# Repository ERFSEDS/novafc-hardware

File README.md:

# Nova Flight Computer

Rev 1.0 hardware:
STM32F401RBTx
USBC - FTDI chip connecting usb to UART2
3 pYRO Channels
SD Card
Flash Chip
High-g Accel: H3LIS331DL
Barometer: MS560702BA03-50
IMU: BMI088
SWDIO

Rev 2.5 hardware:
STM32F411CEUx
USBC
4 Pyro Channels
SD Card
Flash Chip
High-g Accel: H3LIS331DL
Barometer: MS560702BA03-50
IMU: MPU-9250
SWDIO + SWO

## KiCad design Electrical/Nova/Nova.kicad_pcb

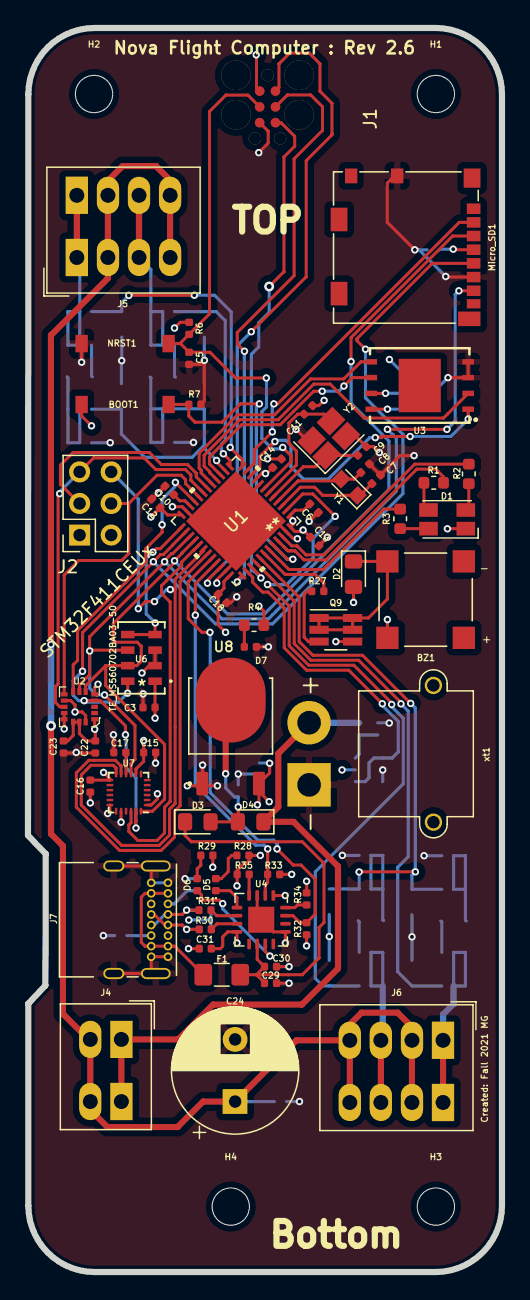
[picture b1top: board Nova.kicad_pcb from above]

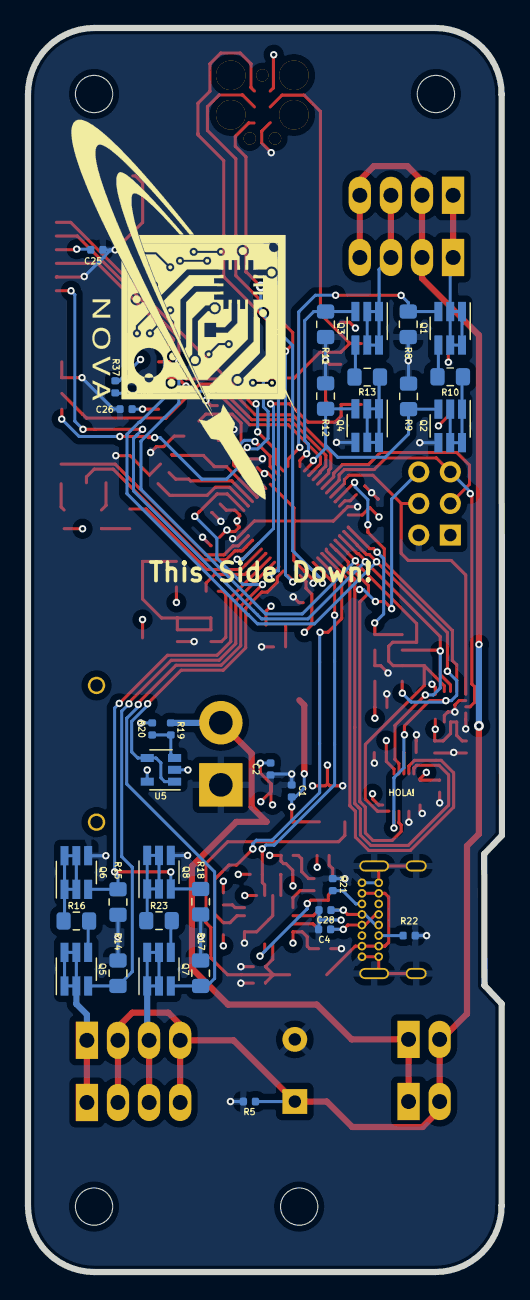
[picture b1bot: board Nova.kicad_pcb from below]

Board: 4 copper layers, 38.1 x 100.1 mm, 102 parts (33 on the bottom side), 79 nets.

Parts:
BOOT1: SW_Push; KSR223GLFG
BZ1: Buzzer; XDCR_CMT-7525-80-SMT-TR
C1, C2, C22: 10uF; C_0402_1005Metric
C3, C5, C6, C12, C13, C14, C16, C17, C18, C23, C25, C29: 100nF; C_0402_1005Metric
C4, C28: 27pF; C_0402_1005Metric
C7, C8, C9, C11: 8pF; C_0402_1005Metric
C10, C30: 4.7uF; C_0402_1005Metric
C15, C31: 10nF; C_0402_1005Metric
C24: 1mF; CP_Radial_D10.0mm_P5.00mm
C26: 0.1uF; C_0402_1005Metric
D1: ASMB-MTB0-0A3A2; LED_Avago_PLCC4_3.2x2.8mm_CW
D2, D3, D4: DIODE; D_0805_2012Metric_Pad1.15x1.40mm_HandSolder
D5, D6, D7: LED; LED_0402_1005Metric
F1: 500mA; Fuse_1206_3216Metric_Pad1.42x1.75mm_HandSolder
H1, H2, H3, H4: MountingHole; MountingHole_3mm
J1: Conn_01x06_Male; j-link_6_pin_needle
J2: Conn_02x04_Counter_Clockwise; PinSocket_2x03_P2.54mm_Vertical
J4: Conn_01x02_Female; TerminalBlock_Phoenix_PTSM-0,5-2-2.5-H-THR_1x02_P2.50mm_Hor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
J5, J6: Conn_01x04_Female; TerminalBlock_Phoenix_PTSM-0,5-4-2.5-H-THR_1x04_P2.50mm_Hor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
J7: USB_C_Receptacle_USB2.0; USB_C_Receptacle_GCT_USB4085
Micro_SD1: WE_693072010801; microSD_HC_Molex_104031-0811
NRST1: SW_Push; KSR223GLFG
Q1, Q2, Q3, Q4, Q5, Q6, Q7, Q8, Q9: Q_NMOS_DGS; SOT-23-6_Handsoldering
R1, R2, R3: 330; R_0603_1608Metric
R4: 5.1k; R_0603_1608Metric
R5, R6, R7, R37: 10k; R_0402_1005Metric
R8, R9, R11, R12, R14, R15, R17, R18: 10k; R_0805_2012Metric_Pad1.15x1.40mm_HandSolder
R10, R13, R16, R23: 3.3; R_0805_2012Metric_Pad1.15x1.40mm_HandSolder
R19: 95.5k; R_0402_1005Metric
R20: 47k; R_0402_1005Metric
R21, R22: 5k; R_0402_1005Metric
R27: 180; R_0402_1005Metric
R28, R29: 270; R_0402_1005Metric
R30, R31, R32, R33, R34, R35: 27; R_0402_1005Metric
U1: STM32F411CEUx; STM32F411CEU6
U2: ST_H3LIS331DL; TFLGA-16_3x3mm
U3: WB_W25N512GVPIT; SON127P800X600X80-9N
U4: FT230XQ; QFN-16-1EP_4x4mm_P0.65mm_EP2.1x2.1mm
U5: OP179GRT; SOT-23-5
U6: TE_MS560702BA03-50; MS560702BA03-50
U7: MPU-9250; InvenSense_QFN-24_3x3mm_P0.4mm
U8: NCP1117-3.3_TO252; DPAK228P968X238-4N
Y1: 32.768kHz; Crystal_SMD_2012-2Pin_2.0x1.2mm_HandSoldering
Y2: 25MHz; Crystal_SMD_EuroQuartz_X22-4Pin_2.5x2.0mm_HandSoldering
xt1: Conn_01x02; AMASS_XT30PW-M_1x02_P2.50mm_Horizontal

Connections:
+3V3: BOOT1.2, BZ1.1 (-), C2.2, C3.1, C6.1, C12.1, C13.1, C14.1, C15.1, C16.1, C18.1, C22.1, C23.2, C25.2, C26.2, C31.2, D1.1 (A), D2.2 (A), J1.1, J2.1, Micro_SD1.4 (VDD), R4.2, R6.1, R28.2, R29.1, R32.1, R33.1, R34.1, R35.1, R37.1, U1.1 (VBAT), U1.9 (VDDA), U1.24 (VDD), U1.36 (VDD), U1.48 (VDD), U2.1 (Vdd_IO), U2.14 (Vdd), U2.15 (Reserved), U3.8 (VCC), U4.1 (VCCIO), U4.8 (3V3OUT), U5.2 (V+), U6.1 (VDD), U7.1 (RESV_VDDIO), U7.8 (VDDIO), U7.13 (VDD), U8.2 (VO)
+BATT: D4.1 (K), J4.1, R19.1, xt1.2
/32CLOCKIN: C7.1, U1.3 (PC14), Y1.1
/32CLOCKOUT: C8.1, U1.4 (PC15), Y1.2
/ACCELEROMETER_CS: U1.21 (PB10), U2.8 (CS)
/ACCEL_INT1: J2.5, U1.19 (PB1), U2.11 (INT_1)
/ACCEL_INT2: J2.4, U1.20 (PB2), U2.9 (INT_2)
/ARM1: Q2.3 (S), Q4.3 (S), R9.1, R12.1, U1.14 (PA4)
/ARM2: Q6.3 (S), Q8.3 (S), R15.1, R18.1, U1.41 (PB5)
/BAROMETER_CS: U1.25 (PB12), U6.4 (SCB), U6.5 (SCB)
/BOOT0: BOOT1.1, R7.1, U1.44 (BOOT0)
/BUZZER: R27.2, U1.42 (PB6)
/CLOCKIN: C9.1, U1.5 (PH0), Y2.1
/CLOCKOUT: C11.1, U1.6 (PH1), Y2.3
/FIRE1: Q1.3 (S), R8.1, U1.12 (PA2)
/FIRE2: Q3.3 (S), R11.1, U1.13 (PA3)
/FIRE3: Q5.3 (S), R14.1, U1.40 (PB4)
/FIRE4: Q7.3 (S), R17.1, U1.2 (PC13)
/FL_CS: U1.10 (PA0), U3.1 (/CS)
/FSYNC: U1.31 (PA10), U7.11 (FSYNC)
/GPIO1: J2.3, U1.18 (PB0)
/IMU_CS: U1.29 (PA8), U7.22 (~CS)
/IMU_INT: J2.6, U1.30 (PA9), U7.12 (INT)
/LED_BLUE: R3.2, U1.43 (PB7)
/LED_GREEN: R1.2, U1.45 (PB8)
/LED_RED: R2.2, U1.46 (PB9)
/NRST: C5.2, J1.3, NRST1.2, R6.2, U1.7 (NRST)
/Pyro Channels/PYRO1: J5.1, Q1.1 (D), Q1.2, Q1.5, Q1.6
/Pyro Channels/PYRO2: J5.3, Q3.1 (D), Q3.2, Q3.5, Q3.6
/Pyro Channels/PYRO3: J6.1, Q5.1 (D), Q5.2, Q5.5, Q5.6
/Pyro Channels/PYRO4: J6.3, Q7.1 (D), Q7.2, Q7.5, Q7.6
/RXD: R33.2, U1.33 (PA12), U4.2 (RXD)
/SD_CS: Micro_SD1.2 (DAT3/CD), U1.11 (PA1)
/SPI1_MISO: U1.16 (PA6), U3.2 (DO(IO1))
/SPI1_MOSI: U1.17 (PA7), U3.5 (DI(IO0))
/SPI1_SCLK: U1.15 (PA5), U3.6 (CLK)
/SPI2_MISO: Micro_SD1.7 (DAT0), U1.27 (PB14), U2.7 (SDO/SA0), U6.6 (SDO), U7.9 (AD0/MISO)
/SPI2_MOSI: Micro_SD1.3 (CMD), U1.28 (PB15), U2.6 (SDA/SDI/SDO), U6.7 (SDI/SDA), U7.24 (SDA/MOSI)
/SPI2_SCLK: Micro_SD1.5 (CLK), U1.26 (PB13), U2.4 (SCL/SPC), U6.8 (SCLK), U7.23 (SCL/SCLK)
/SWCLK: J1.4, U1.37 (PA14)
/SWDIO: J1.2, U1.34 (PA13)
/SWO: J1.6, U1.39 (PB3)
/TXD: R32.2, U1.32 (PA11), U4.15 (TXD)
/USB-C/D+: R31.2, U4.6 (USBDP)
/USB-C/D-: R30.1, U4.7 (USBDM)
/USB-C/_N: C4.1, J7.A7 (D-), J7.B7 (D-), R30.2
/USB-C/_P: C28.1, J7.A6 (D+), J7.B6 (D+), R31.1
/VCAP: C10.1, U1.22 (VCAP1)
/VMonitor: U1.38 (PA15), U5.1, U5.4 (-)
GND: C1.1, C2.1, C3.2, C4.2, C5.1, C6.2, C7.2, C8.2, C9.2, C10.2, C11.2, C12.2, C13.2, C14.2, C15.2, C16.2, C17.2, C18.2, C22.2, C23.1, C24.2, C25.1, C26.1, C28.2, C29.1, C30.1, C31.1, D7.1 (K), J1.5, J2.2, J7.A1 (GND), J7.A12 (GND), J7.B1 (GND), J7.B12 (GND), J7.S1 (SHIELD), Micro_SD1.6 (VSS), Micro_SD1.9 (SHIELD), NRST1.1, Q2.4, Q4.4, Q6.4, Q8.4, Q9.4, R5.2, R7.2, R8.2, R9.2, R11.2, R12.2, R14.2, R15.2, R17.2, R18.2, R20.2, R21.1, R22.2, U1.8 (VSSA), U1.23 (VSS), U1.35 (VSS), U1.47 (VSS), U1.49 (VSS), U2.5 (GND), U2.10 (Reserved), U2.12 (GND), U2.13 (GND), U2.16 (GND), U3.3 (/WP(IO2)), U3.4 (GND), U4.3 (GND), U4.13 (GND), U4.17 (GND), U5.5 (V-), U6.2 (PS), U6.3 (GND), U7.18 (GND), U7.20 (RESV_GND), U8.1 (GND), Y2.2, Y2.4, xt1.1
unnamed: BZ1.2 (+), D2.1 (K), Q9.1 (D), Q9.2, Q9.5, Q9.6
unnamed: C1.2, D3.2 (A), D4.2 (A), U8.3 (VI)
unnamed: C17.1, U7.10 (REGOUT)
unnamed: C24.1, J4.2, J5.2, J5.4, J6.2, J6.4, R5.1
unnamed: D1.2 (BK), R3.1
unnamed: D1.3 (GK), R1.1
unnamed: D1.4 (RK), R2.1
unnamed: D5.1 (K), U4.5 (CBUS2)
unnamed: D5.2 (A), R28.1
unnamed: D6.1 (K), U4.11 (CBUS1)
unnamed: D6.2 (A), R29.2
unnamed: D7.2 (A), R4.1
unnamed: F1.2, J7.A4 (VBUS), J7.A9 (VBUS), J7.B4 (VBUS), J7.B9 (VBUS)
unnamed: J7.A5 (CC1), R21.2
unnamed: J7.B5 (CC2), R22.1
unnamed: Q1.4, R10.1
unnamed: Q2.1 (D), Q2.2, Q2.5, Q2.6, R10.2
unnamed: Q3.4, R13.1
unnamed: Q4.1 (D), Q4.2, Q4.5, Q4.6, R13.2
unnamed: Q5.4, R16.1
unnamed: Q6.1 (D), Q6.2, Q6.5, Q6.6, R16.2
unnamed: Q7.4, R23.1
unnamed: Q8.1 (D), Q8.2, Q8.5, Q8.6, R23.2
unnamed: Q9.3 (S), R27.1
unnamed: R19.2, R20.1, U5.3 (+)
unnamed: R34.2, U4.16 (~RTS)
unnamed: R35.2, U4.4 (~CTS)
unnamed: R37.2, U3.7 (/HOLD(IO3))
VBUS: C29.2, C30.2, D3.1 (K), F1.1, U4.10 (VCC)

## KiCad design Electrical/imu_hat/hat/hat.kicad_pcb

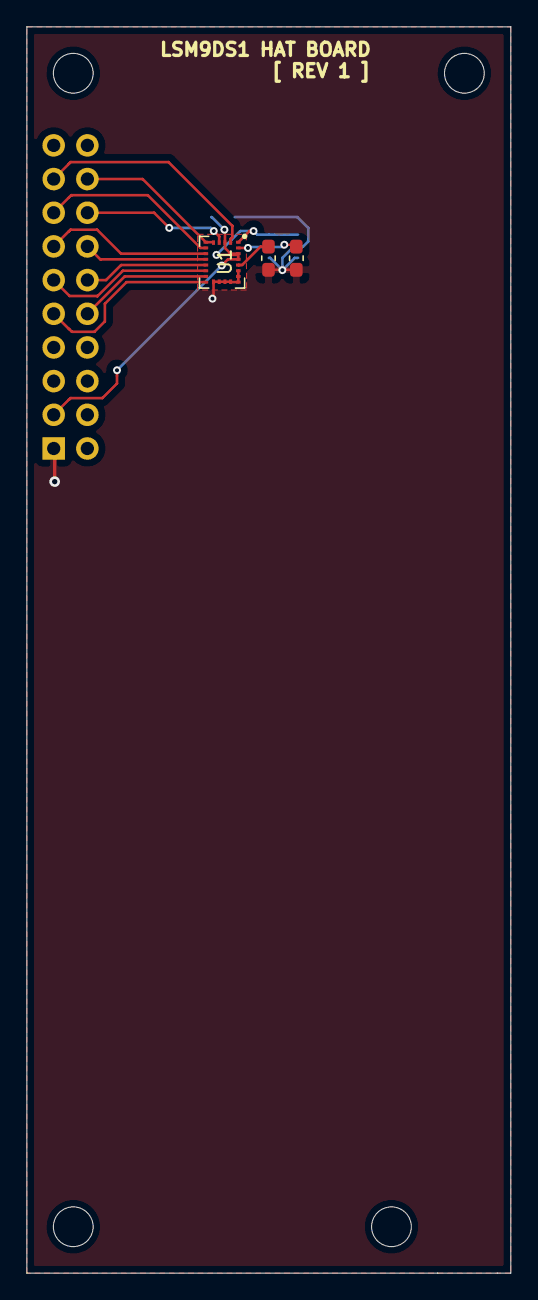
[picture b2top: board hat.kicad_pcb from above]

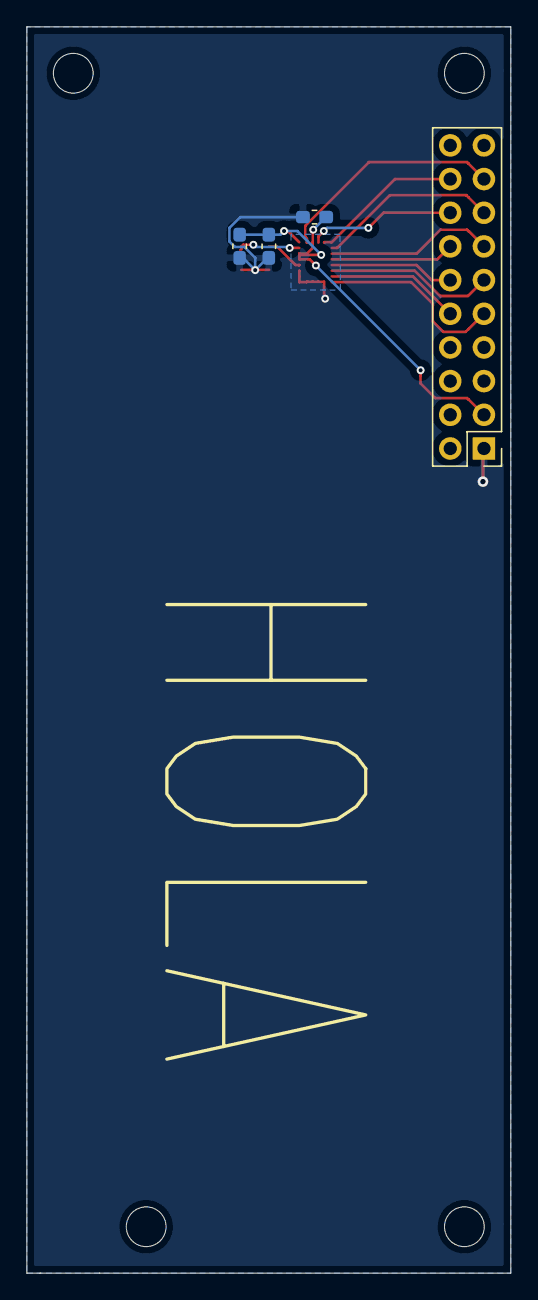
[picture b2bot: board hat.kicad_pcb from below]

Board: 2 copper layers, 36.5 x 94.0 mm, 11 parts (4 on the bottom side), 14 nets.

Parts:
C1: 10nF; C_0603_1608Metric_Pad1.05x0.95mm_HandSolder
C2, C3, C4: 100nF; C_0603_1608Metric_Pad1.05x0.95mm_HandSolder
C5: 10uF; C_0603_1608Metric_Pad1.05x0.95mm_HandSolder
H1, H2, H3, H4: MountingHole; MountingHole_3mm
J1: Conn_02x10_Odd_Even; PinHeader_2x10_P2.54mm_Vertical
U1: LSM9DS1; LGA-24L_3x3.5mm_P0.43mm

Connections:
+3V3: C2.1, C4.1, C5.1, J1.3, U1.1, U1.3, U1.22, U1.23
/CS: J1.15, U1.7
/CSM: J1.13, U1.8
/DEN: J1.9, U1.13
/DRDYM: J1.14, U1.9
/INT1: J1.11, U1.11
/INT2: J1.10, U1.12
/INTM: J1.12, U1.10
/MISO: J1.18, U1.5, U1.6
/MOSI: J1.16, U1.4
/SCLK: J1.17, U1.2
GND: C1.2, C2.2, C3.2, C4.2, C5.2, J1.1, U1.14, U1.15, U1.16, U1.17, U1.18, U1.19, U1.20
unnamed: C1.1, U1.21
unnamed: C3.1, U1.24

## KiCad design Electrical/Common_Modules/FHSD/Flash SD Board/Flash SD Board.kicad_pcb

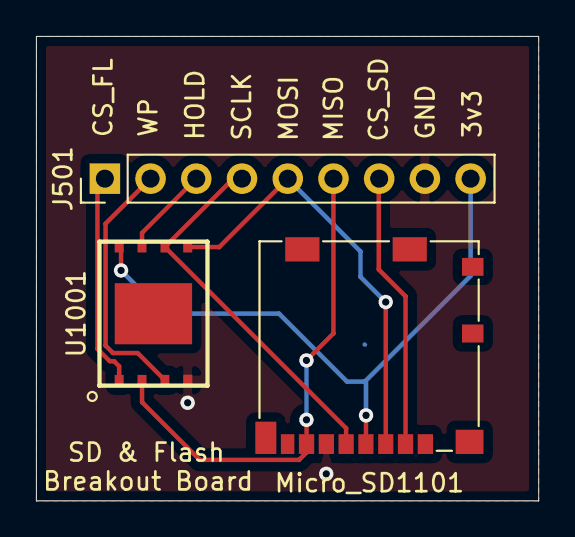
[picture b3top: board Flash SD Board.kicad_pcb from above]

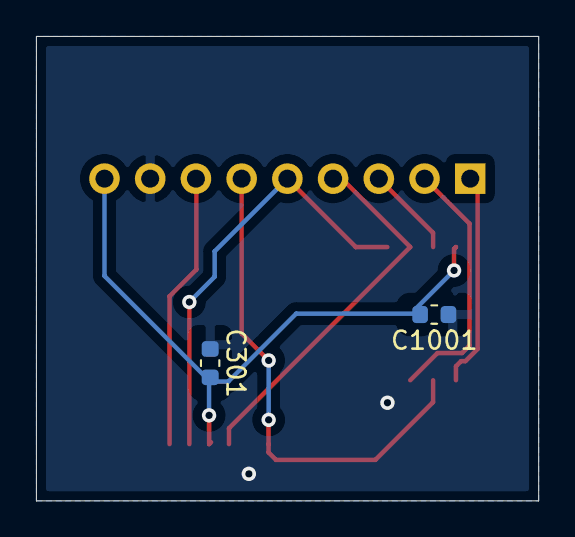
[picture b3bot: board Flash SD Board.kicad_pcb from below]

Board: 2 copper layers, 27.9 x 25.8 mm, 5 parts (2 on the bottom side), 9 nets.

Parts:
C301, C1001: 100nF; C_0603_1608Metric
J501: Conn_01x07_Male; PinHeader_1x09_P2.54mm_Vertical
Micro_SD1101: Micro_SD_Card; microSD_HC_Molex_104031-0811
U1001: W25N512GVPIT

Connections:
+3V3: C301.2, C1001.2, J501.9, Micro_SD1101.4, U1001.8
/main/Flash Chip/CS_FLASH: J501.1, U1001.1
/main/Flash Chip/HOLD: J501.3, U1001.7
/main/Flash Chip/MISO: J501.6, Micro_SD1101.7, U1001.2
/main/Flash Chip/MOSI: J501.5, Micro_SD1101.3, U1001.5
/main/Flash Chip/SCLK: J501.4, Micro_SD1101.5, U1001.6
/main/Flash Chip/WP: J501.2, U1001.3
/main/Headers/CS_SD: J501.7, Micro_SD1101.2
GND: C301.1, C1001.1, J501.8, Micro_SD1101.6, U1001.4

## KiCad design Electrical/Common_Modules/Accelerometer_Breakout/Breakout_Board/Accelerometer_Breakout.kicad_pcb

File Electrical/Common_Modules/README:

This folder is where any circuit section that may be used multiple times is put, for example firing circuit

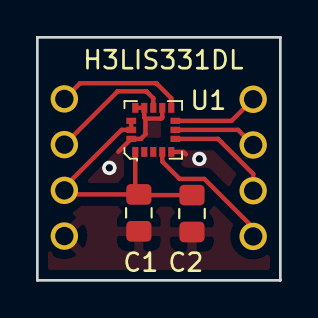
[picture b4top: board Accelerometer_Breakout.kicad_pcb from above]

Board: 2 copper layers, 13.5 x 13.5 mm, 5 parts (0 on the bottom side), 8 nets.

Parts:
C1: 10uf; C_0805_2012Metric_Pad1.15x1.40mm_HandSolder
C2: 0.1uf; C_0805_2012Metric_Pad1.15x1.40mm_HandSolder
U1: H3LIS331DL; TFLGA-16_3x3mm
U2, U3: 4_Pin_header; 4_Pin_Header

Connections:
+3V3: C1.1, C2.2, U1.1, U1.14, U1.15, U2.3
/H3LIS331DL_Accelerometer/CS_ACC: U1.8, U3.4
/H3LIS331DL_Accelerometer/INT_1_ACC: U1.11, U2.2
/H3LIS331DL_Accelerometer/INT_2_ACC: U1.9, U2.1
/H3LIS331DL_Accelerometer/SCL_ACC: U1.4, U3.1
/H3LIS331DL_Accelerometer/SDA_ACC: U1.6, U3.2
/H3LIS331DL_Accelerometer/SDO_ACC: U1.7, U3.3
GND: C1.2, C2.1, U1.5, U1.10, U1.12, U1.13, U1.16, U2.4

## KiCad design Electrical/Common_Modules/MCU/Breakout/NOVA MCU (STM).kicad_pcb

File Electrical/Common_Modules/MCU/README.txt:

This is the Nova Rev 1 Microcontroller Breakout Board. 
Because of the nature of the part, pseudo code will not be written. 
Pseudo code for this part IS the software for Nova. 

Notes: 

Programmable through SWD
debug from USB-C 

3V3 Level logic and voltage levels. 

Fuse and Tantalum capacitor has similar, but different footprints to other parts on the board

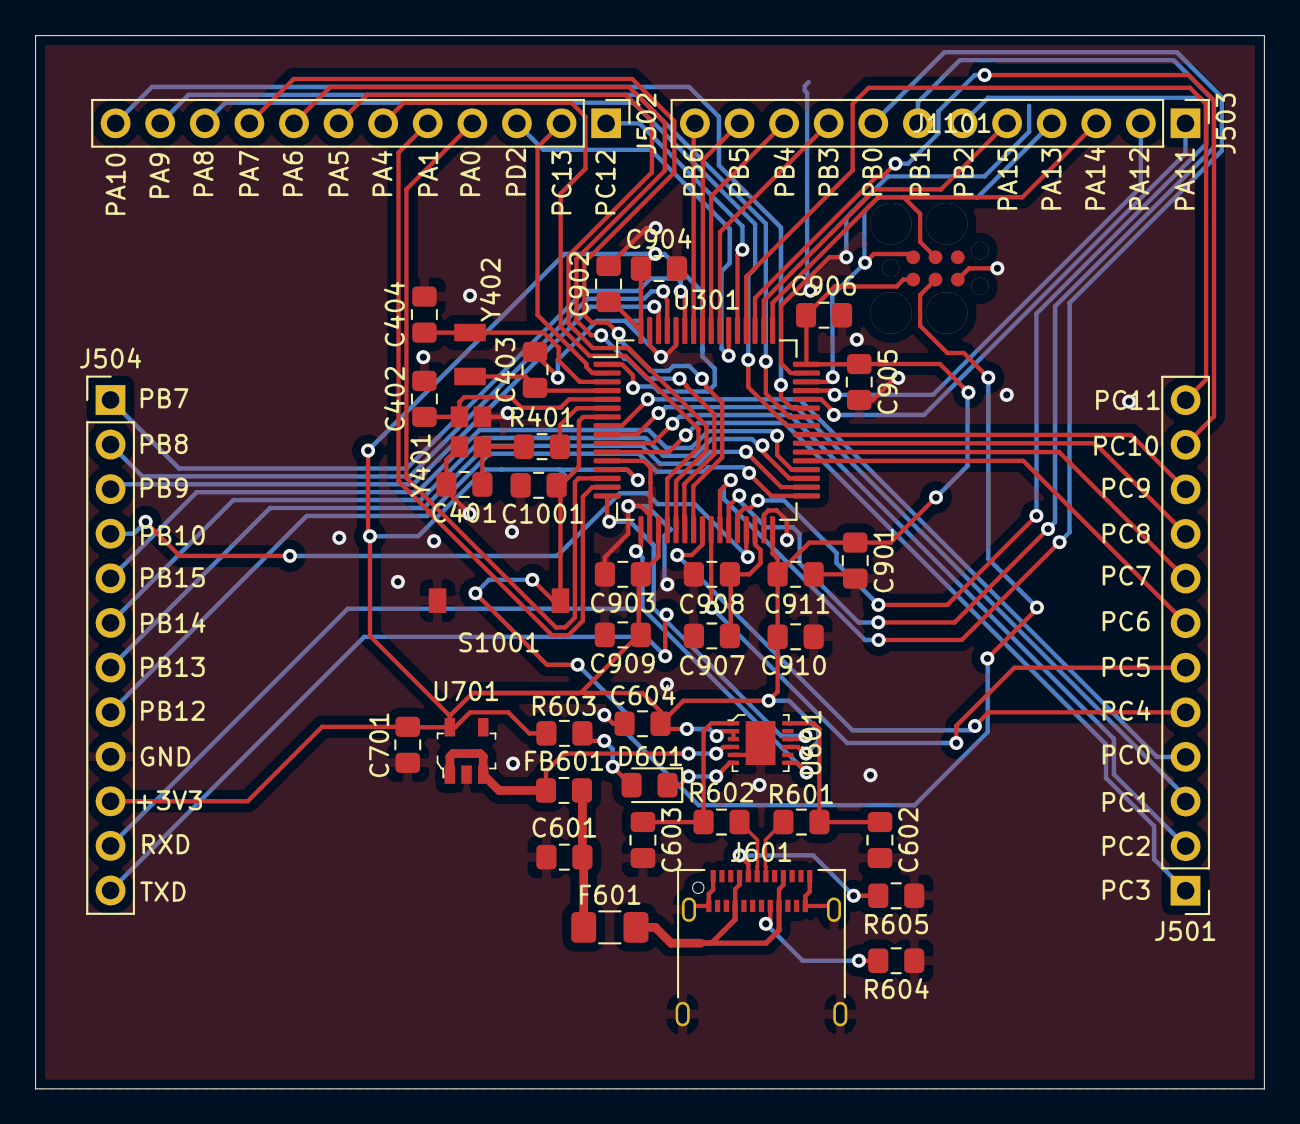
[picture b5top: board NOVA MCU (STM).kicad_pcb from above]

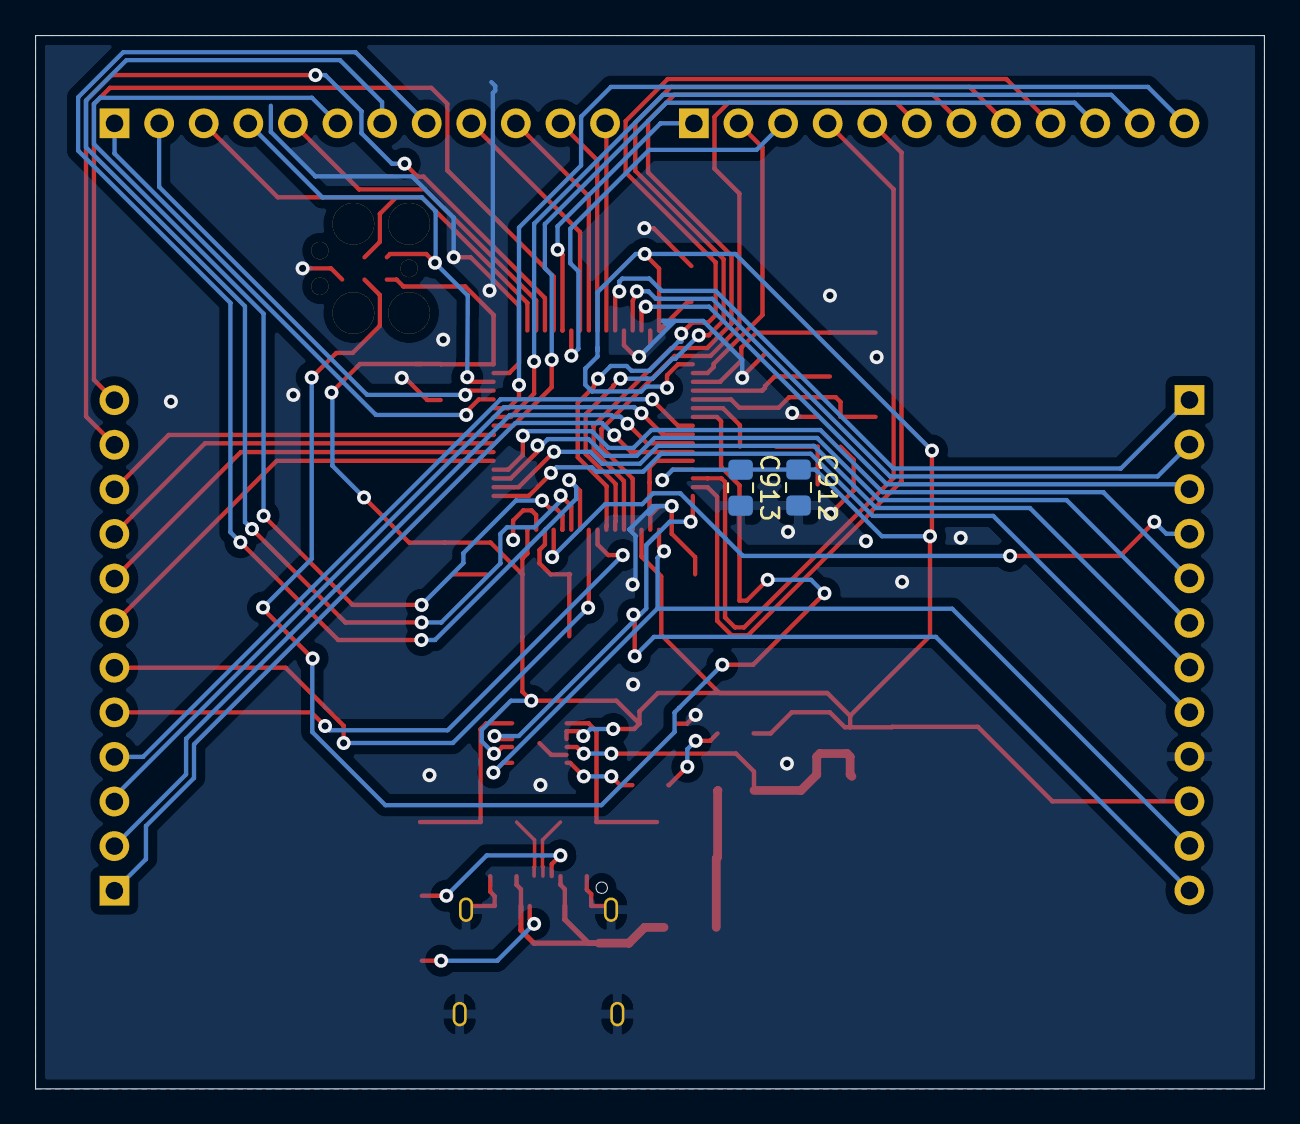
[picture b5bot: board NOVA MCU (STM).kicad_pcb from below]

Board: 2 copper layers, 70.0 x 60.0 mm, 44 parts (2 on the bottom side), 66 nets.

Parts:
C401, C402: 6pF; C_0805_2012Metric_Pad1.15x1.40mm_HandSolder
C403, C404: 2pF; C_0805_2012Metric_Pad1.15x1.40mm_HandSolder
C601: 10nF; C_0805_2012Metric_Pad1.15x1.40mm_HandSolder
C602, C603: 47pF; C_0805_2012Metric_Pad1.15x1.40mm_HandSolder
C604, C901, C902, C903, C904, C905, C906, C910, C912: 100nF; C_0805_2012Metric_Pad1.15x1.40mm_HandSolder
C701, C911, C913: 1uF; C_0805_2012Metric_Pad1.15x1.40mm_HandSolder
C907, C908: 2.2uF; C_0805_2012Metric_Pad1.15x1.40mm_HandSolder
C909: 4.7uF; C_0805_2012Metric_Pad1.15x1.40mm_HandSolder
C1001: 0.1uF; C_0805_2012Metric_Pad1.15x1.40mm_HandSolder
D601: LED; LED_0805_2012Metric_Pad1.15x1.40mm_HandSolder
F601: 500mA; Fuse_1206_3216Metric_Pad1.42x1.75mm_HandSolder
FB601: 600 OHM; R_0805_2012Metric_Pad1.15x1.40mm_HandSolder
J501, J502, J503, J504: Conn_01x12_Male; PinHeader_1x12_P2.54mm_Vertical
J601: USB_C_Receptacle; USB_C_Receptacle_Amphenol_12401610E4-2A
J1101: Conn_01x06_Male; j-link_6_pin_needle
R401: TBD; R_0805_2012Metric_Pad1.15x1.40mm_HandSolder
R601, R602: 27 OHM; R_0805_2012Metric_Pad1.15x1.40mm_HandSolder
R603: 270 OHM; R_0805_2012Metric_Pad1.15x1.40mm_HandSolder
R604, R605: 5K; R_0805_2012Metric_Pad1.15x1.40mm_HandSolder
S1001: KSR223GLFG
U301: STM32F401RBTx; LQFP-64_10x10mm_P0.5mm
U601: FT234XD-R; DFN-12-1EP_3x3mm
U701: MIC5219-3_3YM5-TR; SOT-753
Y401: ECS-260-8-36B-CKY-TR; ECX-2236B
Y402: JTX310

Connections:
+3V3: C604.1, C701.1, C901.1, C902.1, C903.1, C904.1, C905.1, C906.1, C909.1, C910.1, C911.1, C912.1, C913.1, J504.10, J1101.1, R603.2, U301.1, U301.13, U301.19, U301.32, U301.48, U301.64, U601.2, U601.3, U601.9, U701.5
/STM32F401RBT6/Clocks/CLOCKIN: C402.1, U301.5, Y401.3
/STM32F401RBT6/Clocks/CLOCKOUT: R401.2, U301.6
/STM32F401RBT6/Clocks/RTCCRYSTALIN: C404.1, U301.3, Y402.2
/STM32F401RBT6/Clocks/RTCCRYSTALOUT: C403.1, U301.4, Y402.1
/STM32F401RBT6/FILTERING/VCAP: C907.2, C908.2, U301.30
/STM32F401RBT6/MCU/RESET: C1001.1, J1101.3, S1001.2, U301.7
/STM32F401RBT6/Pin Headers/1: J501.4, U301.8
/STM32F401RBT6/Pin Headers/2: J501.3, U301.9
/STM32F401RBT6/Pin Headers/3: J501.2, U301.10
/STM32F401RBT6/Pin Headers/4: J501.1, U301.11
/STM32F401RBT6/Pin Headers/5: J501.5, U301.24
/STM32F401RBT6/Pin Headers/6: J501.6, U301.25
/STM32F401RBT6/Pin Headers/7: J501.7, U301.37
/STM32F401RBT6/Pin Headers/8: J501.8, U301.38
/STM32F401RBT6/Pin Headers/9: J501.9, U301.39
/STM32F401RBT6/Pin Headers/10: J501.10, U301.40
/STM32F401RBT6/Pin Headers/11: J501.11, U301.51
/STM32F401RBT6/Pin Headers/12: J501.12, U301.52
/STM32F401RBT6/Pin Headers/13: J502.1, U301.53
/STM32F401RBT6/Pin Headers/14: J502.2, U301.2
/STM32F401RBT6/Pin Headers/15: J502.3, U301.54
/STM32F401RBT6/Pin Headers/16: J502.4, U301.14
/STM32F401RBT6/Pin Headers/17: J502.5, U301.15
/STM32F401RBT6/Pin Headers/18: J502.6, U301.20
/STM32F401RBT6/Pin Headers/19: J502.7, U301.21
/STM32F401RBT6/Pin Headers/20: J502.8, U301.22
/STM32F401RBT6/Pin Headers/21: J502.9, U301.23
/STM32F401RBT6/Pin Headers/22: J502.10, U301.41
/STM32F401RBT6/Pin Headers/23: J502.11, U301.42
/STM32F401RBT6/Pin Headers/24: J502.12, U301.43
/STM32F401RBT6/Pin Headers/25: J503.1, U301.44
/STM32F401RBT6/Pin Headers/26: J503.2, U301.45
/STM32F401RBT6/Pin Headers/29: J503.5, U301.50
/STM32F401RBT6/Pin Headers/30: J503.8, U301.26
/STM32F401RBT6/Pin Headers/31: J503.7, U301.27
/STM32F401RBT6/Pin Headers/32: J503.6, U301.28
/STM32F401RBT6/Pin Headers/33: J503.9, U301.55
/STM32F401RBT6/Pin Headers/34: J503.10, U301.56
/STM32F401RBT6/Pin Headers/35: J503.11, U301.57
/STM32F401RBT6/Pin Headers/36: J503.12, U301.58
/STM32F401RBT6/Pin Headers/37: J504.1, U301.59
/STM32F401RBT6/Pin Headers/38: J504.2, U301.61
/STM32F401RBT6/Pin Headers/39: J504.3, U301.62
/STM32F401RBT6/Pin Headers/40: J504.4, U301.29
/STM32F401RBT6/Pin Headers/41: J504.8, U301.33
/STM32F401RBT6/Pin Headers/42: J504.7, U301.34
/STM32F401RBT6/Pin Headers/43: J504.6, U301.35
/STM32F401RBT6/Pin Headers/44: J504.5, U301.36
/STM32F401RBT6/RXD: J504.11, U301.17, U601.7
/STM32F401RBT6/SWCLK: J503.3, J1101.4, U301.49
/STM32F401RBT6/SWDIO: J503.4, J1101.2, U301.46
/STM32F401RBT6/TXD: J504.12, U301.16, U601.10
/STM32F401RBT6/USB-C/D1+: J601.A6, R602.2
/STM32F401RBT6/USB-C/D1-: J601.A7, R601.2
/STM32F401RBT6/USB-C/D2+: C603.1, R602.1, U601.1
/STM32F401RBT6/USB-C/D2-: C602.1, R601.1, U601.12
GND: C401.2, C402.2, C403.2, C404.2, C601.1, C602.2, C603.2, C604.2, C701.2, C901.2, C902.2, C903.2, C904.2, C905.2, C906.2, C907.1, C908.1, C909.2, C910.2, C911.2, C912.2, C913.2, C1001.2, J504.9, J601.A1, J601.A12, J601.B1, J601.B12, J601.S1, J1101.5, R604.1, R605.1, S1001.1, U301.12, U301.18, U301.31, U301.47, U301.60, U301.63, U601.5, U601.13, U701.2, Y401.2, Y401.4
unnamed: C401.1, R401.1, Y401.1
unnamed: C601.2, F601.1, FB601.2
unnamed: D601.1, U601.6
unnamed: D601.2, R603.1
unnamed: F601.2, J601.A4, J601.A9, J601.B4, J601.B9
unnamed: J601.A5, R605.2
unnamed: J601.B5, R604.2
VBUS: FB601.1, U601.4, U701.1, U701.3

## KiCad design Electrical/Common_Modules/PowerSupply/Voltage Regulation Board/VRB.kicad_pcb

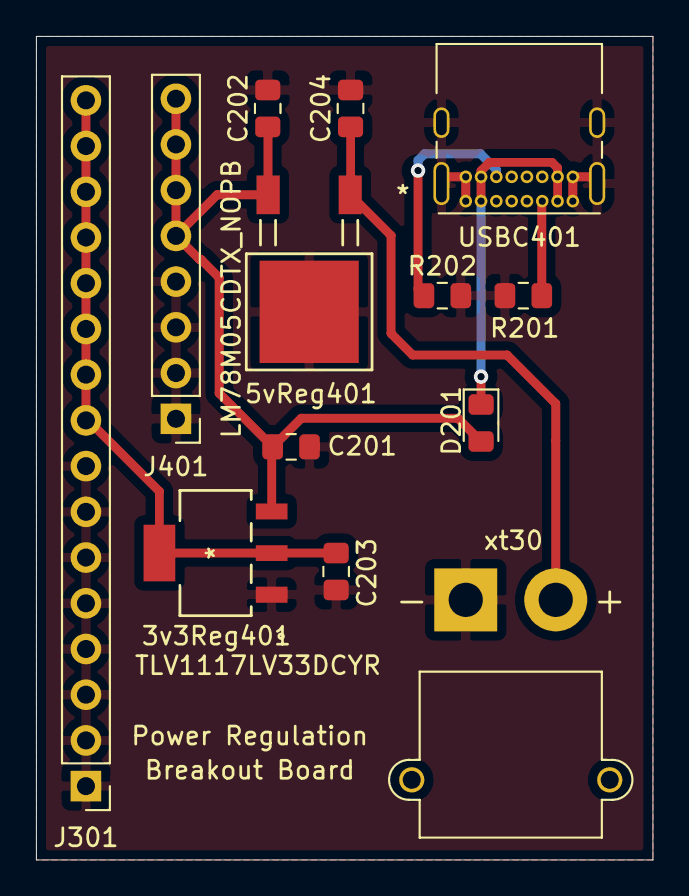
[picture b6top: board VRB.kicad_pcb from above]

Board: 2 copper layers, 34.2 x 45.8 mm, 13 parts (0 on the bottom side), 7 nets.

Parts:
3v3Reg401: TLV1117LV33DCYR
5vReg401: LM78M05CDTX_NOPB; LM78M05CDTX&slash_NOPB
C201: 0.33 uF; C_0805_2012Metric_Pad1.15x1.40mm_HandSolder
C202, C204: 1 uF; C_0805_2012Metric_Pad1.15x1.40mm_HandSolder
C203: 0.1 uF; C_0805_2012Metric_Pad1.15x1.40mm_HandSolder
D201: DIODE; D_0805_2012Metric_Pad1.15x1.40mm_HandSolder
J301: 16PinConnector; PinHeader_1x16_P2.54mm_Vertical
J401: 8PinConnector; PinHeader_1x08_P2.54mm_Vertical
R201, R202: 5k; R_0805_2012Metric_Pad1.15x1.40mm_HandSolder
USBC401: USB_C_2.0; USB_C_Receptacle_GCT_USB4085
xt30: Conn_01x02; AMASS_XT30PW-M_1x02_P2.50mm_Horizontal

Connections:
+3V3: 3v3Reg401.2, 3v3Reg401.4, C203.2, J301.9, J301.10, J301.11, J301.12, J301.13, J301.14, J301.15, J301.16
+5V: 3v3Reg401.3, 5vReg401.3, C201.1, C202.1, D201.2, J401.5, J401.6, J401.7, J401.8
GND: 3v3Reg401.1, 5vReg401.2, C201.2, C202.2, C203.1, C204.2, J301.1, J301.2, J301.3, J301.4, J301.5, J301.6, J301.7, J301.8, J401.1, J401.2, J401.3, J401.4, R201.1, R202.2, USBC401.A1, USBC401.A12, USBC401.B1, USBC401.B12, USBC401.S1, xt30.1
unnamed: 5vReg401.1, C204.1, xt30.2
unnamed: D201.1, USBC401.A4, USBC401.A9, USBC401.B4, USBC401.B9
unnamed: R201.2, USBC401.A5
unnamed: R202.1, USBC401.B5

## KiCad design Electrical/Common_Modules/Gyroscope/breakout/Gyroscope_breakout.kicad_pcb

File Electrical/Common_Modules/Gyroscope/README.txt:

The Gyroscope is more accurately described as an IMU, it allows for reading both
rotational information as a Gyroscope however it also allows for reading 
accelleration values less that 24g which makes it not ideal for the requirements 
so a dedicated accelerometer is also used. 

The IMU also has a temperature sensor that can be used to monitor the temperature
inside the rocket.

THe Gyroscope supports both I2C and SPI, however due to the prefference of SPI,
that is the only protocol that will be covered here, for information in I2C refer
to the datasheet

It also appears that there are interupts that can be used to trigger events, say 
engine ignition for a rocket.

TO read data from this sensor format data as follows
uint16_t SPI_DATA = (0x7F & reg_addr) << 8
spi_send(addr, SPI_DATA)
	NOTE: some registers return 1 byte and some return 2!
	Data is read during the 2nd byte
To write Data to this sensor use the following
uint16_t SPI_DATA = ((0x80 | reg_addr) << 8 ) | DATA_BYTE
spi_send(addr, SPI_DATA)

Important registers

Register Name: Register Value
Register Purpose

ACC_STATUS: 0x03
Gives the status of the data in the accelerometer

ACC_Data: 0x12-0x17
Data for the accelerometers in 2's compliment each axis split into two registers

ACC_INT_STATUS: 0x1D
Acceleration data ready input cleared on read of this register

ACC_CONFIG: 0x40
Configuration for Accelerometer

ACC_RANGE: 0x41
Acceleration range for the Acceleromter (0x03 is 24G)

ACC_SELF_TEST: 0x6D
Enables the self test signal

ACC_PWR: 0x7C-7E
Power mode for the acceleroemter(on, off, suspend, reset)

Rate_Data: 0x02-0x07
Contains the angular velocity sensor output, stored in a similar matter to 
ACC_Data

GYRO_INT_STAT: 0x0A
Interupt status for the gyro

GYRO_RANGE: 0x0F
Range for the Gyroscope

GYRO_BANDWIDTH: 0x10
Bandwidth that the gyroscope data can be read at

GYRO_PWR: 0x11, 0x14
Power modes for gyroscope

GYRO_INT_CTL: 0x15
Enable interupt for gyro

GYRO_SELF_TEST: 0x3C
Enables the self test for the gyro

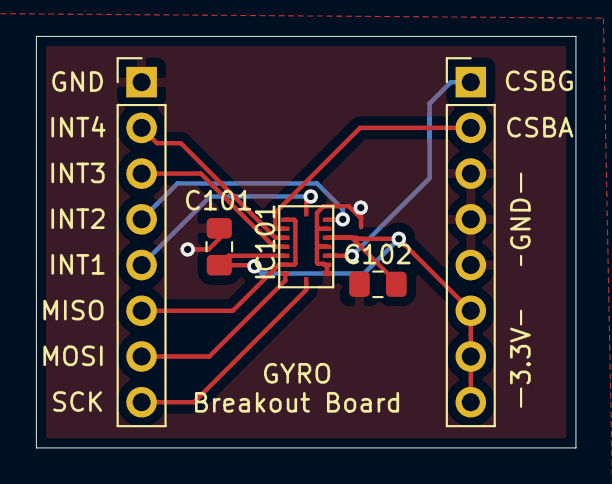
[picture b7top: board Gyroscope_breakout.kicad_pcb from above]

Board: 2 copper layers, 30.0 x 22.9 mm, 5 parts (0 on the bottom side), 11 nets.

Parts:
C101, C102: 100nF; C_0805_2012Metric_Pad1.15x1.40mm_HandSolder
IC101: BMI088; 16-LGA-(4.5x3)
J101: Conn_01x08; PinHeader_1x08_P2.54mm_Vertical
e101: Conn_01x08; PinHeader_1x08_P2.54mm_Vertical

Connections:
+3V3: C101.2, C102.2, IC101.3, IC101.11, e101.6, e101.7, e101.8
/CSB_ACCEL: IC101.14, e101.2
/CSB_GYRO: IC101.5, e101.1
/INT1_ACCEL: IC101.16, J101.5
/INT2_ACCEL: IC101.1, J101.4
/INT3_GYRO: IC101.12, J101.3
/INT4_GYRO: IC101.13, J101.2
/MISO: IC101.10, IC101.15, J101.6
/MOSI: IC101.9, J101.7
/SCK: IC101.8, J101.8
GND: C101.1, C102.1, IC101.2, IC101.4, IC101.6, IC101.7, J101.1, e101.3, e101.4, e101.5

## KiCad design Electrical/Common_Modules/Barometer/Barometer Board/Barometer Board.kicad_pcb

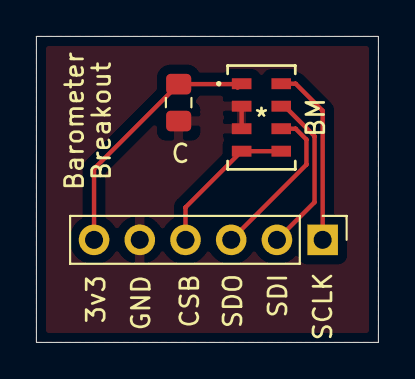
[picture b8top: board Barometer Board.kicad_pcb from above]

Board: 2 copper layers, 19.0 x 17.0 mm, 3 parts (0 on the bottom side), 6 nets.

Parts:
BM: MS560702BA03-50
C: 100nF; C_0805_2012Metric_Pad1.15x1.40mm_HandSolder
Header-Pins301: Conn_01x06_Male; PinHeader_1x06_P2.54mm_Vertical

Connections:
+3V3: BM.1, C.1, Header-Pins301.6
/Barometer/CSB: BM.4, BM.5, Header-Pins301.4
/Barometer/SCLK: BM.8, Header-Pins301.1
/Barometer/SDI: BM.7, Header-Pins301.2
/Barometer/SDO: BM.6, Header-Pins301.3
GND: BM.2, BM.3, C.2, Header-Pins301.5

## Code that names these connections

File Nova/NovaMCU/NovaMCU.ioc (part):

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Mcu.Name=STM32F411C(C-E)Ux
Mcu.Package=UFQFPN48
Mcu.UserName=STM32F411CEUx
PA0-WKUP.GPIOParameters=GPIO_Label
PA0-WKUP.GPIO_Label=FL_CS
PA0-WKUP.Signal=GPIO_Output
PA1.GPIOParameters=GPIO_Label
PA1.GPIO_Label=SD_CS
PA1.Signal=GPIO_Output
PA10.GPIOParameters=GPIO_Label
PA10.GPIO_Label=FSYNC
PA10.Signal=GPIO_Output
PA11.Mode=Asynchronous
PA11.Signal=USART6_TX
PA12.Mode=Asynchronous
PA12.Signal=USART6_RX
PA13.Mode=Trace_Asynchronous_SW
PA13.Signal=SYS_JTMS-SWDIO
PA14.Mode=Trace_Asynchronous_SW
PA14.Signal=SYS_JTCK-SWCLK
PA15.GPIOParameters=GPIO_Label
PA15.GPIO_Label=V_MONITOR
PA15.Signal=GPIO_Analog
PA2.GPIOParameters=GPIO_Label
PA2.GPIO_Label=FIRE1
PA2.Signal=GPIO_Output
PA3.GPIOParameters=GPIO_Label
PA3.GPIO_Label=FIRE2
PA3.Signal=GPIO_Output
PA4.GPIOParameters=GPIO_Label
PA4.GPIO_Label=ARM1
PA4.Signal=GPIO_Output
PA5.Mode=Full_Duplex_Master
PA5.Signal=SPI1_SCK
PA6.Mode=Full_Duplex_Master
PA6.Signal=SPI1_MISO
PA7.Mode=Full_Duplex_Master
PA7.Signal=SPI1_MOSI
PA8.GPIOParameters=GPIO_Label
PA8.GPIO_Label=IMU_CS
PA8.Signal=GPIO_Output
PA9.GPIOParameters=GPIO_Label
PA9.GPIO_Label=IMU_INT
PA9.Signal=GPIO_Output
PB0.GPIOParameters=GPIO_Label
PB0.GPIO_Label=GPIO2
PB0.Signal=GPIO_Output
PB1.GPIOParameters=GPIO_Label
PB1.GPIO_Label=INT1
PB1.Signal=GPIO_Output
PB10.GPIOParameters=GPIO_Label
PB10.GPIO_Label=ACCELEROMETER_CS
PB10.Signal=GPIO_Output
PB12.GPIOParameters=GPIO_Label
PB12.GPIO_Label=BAROMETER_CS
PB12.Signal=GPIO_Output
PB13.Mode=Full_Duplex_Master
PB13.Signal=SPI2_SCK
PB14.Mode=Full_Duplex_Master
PB14.Signal=SPI2_MISO
PB15.Mode=Full_Duplex_Master
PB15.Signal=SPI2_MOSI
PB2.GPIOParameters=GPIO_Label
PB2.GPIO_Label=INT2
PB2.Signal=GPIO_Output
PB3.Mode=Trace_Asynchronous_SW
PB3.Signal=SYS_JTDO-SWO
PB4.GPIOParameters=GPIO_Label
PB4.GPIO_Label=FIRE3
PB4.Signal=GPIO_Output
PB5.GPIOParameters=GPIO_Label
PB5.GPIO_Label=ARM2
PB5.Signal=GPIO_Output
PB6.GPIOParameters=GPIO_Label
PB6.GPIO_Label=BUZZER
PB6.Signal=GPIO_Output
PB7.GPIOParameters=GPIO_Label
PB7.GPIO_Label=LED_BLUE
PB7.Signal=GPIO_Output
PB8.GPIOParameters=GPIO_Label
PB8.GPIO_Label=LED_GREEN
PB8.Signal=GPIO_Output
PB9.GPIOParameters=GPIO_Label
PB9.GPIO_Label=LED_RED
PB9.Signal=GPIO_Output
PC13-ANTI_TAMP.GPIOParameters=GPIO_Label
PC13-ANTI_TAMP.GPIO_Label=FIRE4
PC13-ANTI_TAMP.Signal=GPIO_Output
PC14-OSC32_IN.Mode=LSE-External-Oscillator
PC14-OSC32_IN.Signal=RCC_OSC32_IN
PC15-OSC32_OUT.Mode=LSE-External-Oscillator
PC15-OSC32_OUT.Signal=RCC_OSC32_OUT
PH0\ -\ OSC_IN.Mode=HSE-External-Oscillator
PH0\ -\ OSC_IN.Signal=RCC_OSC_IN
PH1\ -\ OSC_OUT.Mode=HSE-External-Oscillator
PH1\ -\ OSC_OUT.Signal=RCC_OSC_OUT
RCC.HSE_VALUE=25000000
RCC.SYSCLKFreq_VALUE=16000000
board=custom

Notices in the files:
parts and their libraries:
Copyright 2016 Accelerated Designs. All rights reserved.
Copyright 2021 Accelerated Designs. All rights reserved.
